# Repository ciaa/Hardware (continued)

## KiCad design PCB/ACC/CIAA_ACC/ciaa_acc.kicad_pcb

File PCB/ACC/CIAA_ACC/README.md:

# CIAA-ACC

Here you will find KiCad design files, [gerber files](output_files) and some [documentation](doc) for this board
developed by [INTI Argentina](http://www.inti.gob.ar/) - [CMNB](http://www.inti.gob.ar/microynanoelectronica/) with the collaboration of [ACSE](http://www.sase.com.ar/asociacion-civil-sistemas-embebidos), [CADIEEL](http://www.cadieel.org.ar) and [Emtech S.A.](http://www.emtech.com.ar) as part of the [CIAA project](http://www.proyecto-ciaa.com.ar/).
Also you can visit [CIAA-ACC Wiki Page](http://www.proyecto-ciaa.com.ar/devwiki/doku.php?id=desarrollo:ciaa_acc:ciaa_acc_inicio).

 - [Authors](doc/AUTHORS.md).
 - License: [CIAA Hardware license](../../../LICENSE).

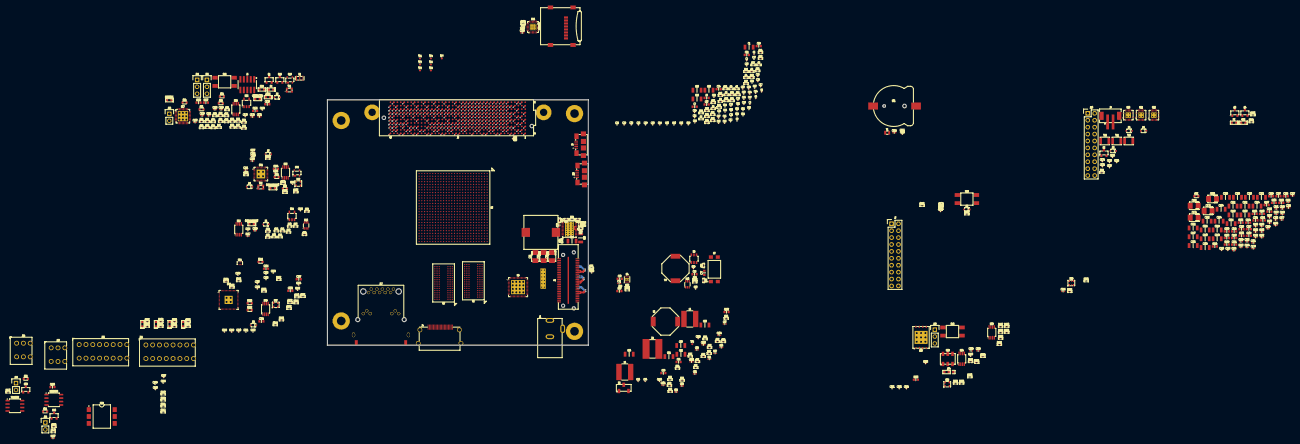
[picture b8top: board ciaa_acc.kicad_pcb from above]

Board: 12 copper layers, 571 parts (0 on the bottom side), 650 nets.

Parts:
BT1: CR1220; BC501SM
C1, C28, C55, C56, C65, C66, C80, C81, C82, C83, C86, C161, C163, C167, C180, C199, C203, C208, C216, C218, C220, C221, C222, C224, C226, C228, C230, C231, C232, C234: 100uF; c_1206
C2, C5, C10, C13, C16, C19, C22, C25, C29, C32, C37, C40, C43, C46, C49, C52, C59, C60, C69, C89, C93, C94, C95, C105, C106, C107, C108, C109, C110, C111, C115, C116, C123, C124, C132, C133, C134, C135, C136, C137, C142, C143, C144, C145, C146, C147, C148, C149, C151, C152, C153, C154, C248, C249, C250, C251, C253, C254, C255, C257, C258, C262, C263, C265, C267, C268: 100nF; c_0201
C3, C6, C8, C9, C11, C12, C14, C15, C17, C18, C20, C21, C23, C24, C26, C27, C30, C33, C35, C36, C38, C39, C41, C42, C44, C45, C47, C48, C50, C51, C53, C54, C61, C62, C63, C64, C150, C223, C225, C242, C243, C259, C269, C270, C271, C272, C273, C274, C275: 10nF; c_0201
C4, C7, C31, C34, C57, C58, C68, C70, C77, C90, C96, C122, C125, C126, C127, C155, C156, C160, C165, C169, C171, C173, C175, C178, C182, C184, C186, C188, C190, C194, C197, C204, C205, C206, C207, C209, C210, C211, C227, C229, C233, C246, C247, C252, C264: 10uF; c_0603
C67: 470nF; c_0402
C71: 220nF; c_0402
C72, C87: 2.2nF; c_0402
C73: 47nF; c_0402
C74: 22nF; c_0402
C75, C119, C120, C121: 1nF; c_0402
C76, C78, C79, C162, C166, C170, C174: 330uF; tant_B_3528
C84, C85, C97, C98: 68nF; c_0402
C88, C101: 1.2nF; c_0402
C91: 24pF; c_0402
C92: 11pF; c_0402
C99, C244: 4.7uF; c_0603
C100, C138, C139, C140, C141: 1.5nF; c_0402
C102: 3.3uF; c_0603
C103: 16pF; c_0402
C104: 13pF; c_0402
C112, C113: 18pF; c_0201
C114, C117, C118, C128, C129, C130, C131, C157, C158, C159, C238, C239, C240, C245, C256, C261, C266: 100nF; c_0402
C164, C168, C172, C176, C177, C179, C181, C183, C185, C187, C189, C191, C192, C193, C195, C196, C198, C200, C201, C202, C213, C215, C217, C219, C235, C236, C241, C260: 1uF; c_0402
C212, C214: 10uF; c_1206
C237: 2.2uF; c_0402
D1, D4, D5: PESD3V3U1UA; SOD-323
D2, D3, D6, D7, D9: 1N4148; SOD-323
D8: SD05T1G; SOD-323
DS1, DS11: OVERCURRENT; LED-0603
DS2, DS13: ERR; LED-0603
DS3, DS12: OK; LED-0603
DS4: DONE; LED-0603
DS5: CONNECTED; LED-0603
DS6: RUNNING; LED-0603
DS7, DS8, DS9, DS10: LED; LED-0603
FB1, FB2, FB10, FB11, FB12: MPZ1608S601ATA00; l_0603
FB3, FB7, FB8: BLM18KG221SN1D; l_0603
FB4, FB5, FB6, FB9: MMZ1608B601CTAH0; l_0603
H1, H2, H3, H4: PCB_HOLE; PCIE104_HOLE
J1: 5V 5A; POWER_JACK
J2: OneBank Top; ASP-129637-13
J3: OneBank Bottom; ASP-129646-22
J4: HDMI; 10029449-111RLF
J5: FMC_HPC; ASP-134486-01
J6: JTAG DIRECT; PIN_ARRAY_5x2_1.27_SMD
J7, J10: DNP; Pin_Header_Straight_2x10
J8: USB Micro B; ZX62-AB-5PA
J9: FAN; B2B-PH-SM4-TB
J11: DIGITAL IN; 1770940
J12: DIGITAL OUT; 1770940
J13: UART0; Pin_Header_Straight_1x03
J14: CAN; 1770898
J15: RS485; 1770898
J16: USB Micro AB; ZX62-AB-5PA
J17: 1840461-1
J18: microSD; MicroSD_Hinged
JP1, JP2: JUMPER3; Pin_Header_Straight_1x03
JP3, JP5, JP6: JUMPER; Pin_Header_Straight_1x02
JP4: PLL; JUMPER3_0603
L1: 220nH; SRP1238A
L2, L5: 3uH; SRU1048
L3, L6: 4.7uH; SRN6045
L4: 6.2uH; SRR6038
Q1: DMP3099L; SOT-23
Q2, Q3, Q4: BSS806N; SOT-23
R1, R2, R27: 80.6; r_0402
R3, R4, R5, R6, R7, R8, R9, R10, R11, R12, R13, R14, R15, R16, R17, R18, R19, R20, R21, R22, R23, R24, R25, R26: 40.2; r_0402
R28, R79, R80, R92, R125, R130, R131, R133, R140, R145: 4.7K; r_0402
R29, R30: 240; r_0402
R31, R32, R45, R46, R50, R57, R59, R64, R119, R120, R141, R142, R146: 10K; r_0402
R33: 200K; r_0402
R34, R36, R49, R98: 100K; r_0402
R35, R103, R104, R105, R106, R135, R147, R148, R152: 1K; r_0402
R37: 309K; r_0402
R38: 2; r_0402
R39: 10.7K; r_0402
R40: 174K; r_0402
R41: 39.2K; r_0402
R42: 3; r_0402
R43, R81, R82, R83, R84, R85, R86, R115, R116, R137, R143, R153: 100; r_0402
R44: 6.49K; r_0402
R47: 6.81K; r_0402
R48: 8.87K; r_0402
R51, R121, R122, R123, R124, R126, R129: 20K; r_0402
R52, R63: 16K; r_0402
R53: 6.65K; r_0402
R54: 13.3K; r_0402
R55: 11.3K; r_0402
R56: 11K; r_0402
R58: 182K; r_0402
R60: 75K; r_0402
R61: 24K; r_0402
R62: 14K; r_0402
R65: 5.1K; r_0402
R66, R67, R149: DNP; r_0402
R68, R69, R70, R71, R72, R73, R74, R76, R132: 49R9; r_0402
R75: 51K; r_0402
R77: 27K; r_0402
R78, R134: 680; r_0402
R87: 2K2; r_0402
R88: 3K3; r_0402
R89: 1.5K; r_0402
R90, R91, R95, R97: 33; r_0402
R93, R155: 330; r_0402
R94, R96, R150, R151, R154: 220; r_0402
R99, R100, R101, R102: 4.7K 1/4W; r_1206
R107, R108, R109, R110: 33K; r_0402
R111, R112, R113, R114: 560; r_0402
R117, R118: 2.2K; r_0402
R127, R128: 120; r_0402
R136: 8.06K; r_0402
R138, R139: 1.0K; r_0402
R144: 12.1K; r_0402
RP1: 10K; r_0402_4
SW1: PROG_B; TACT_SMD_4.5X4.5
SW2: POR_B; TACT_SMD_4.5X4.5
SW3: SRST; TACT_SMD_4.5X4.5
TH1, TH2, TH3: PTC 0.5A; ptc_1210
TP1, TP2, TP3, TP4, TP5, TP6, TP7, TP8: TESTPOINT
TR1, TR2: SRF2012
U1: XC7Z030-2FBG676I; FBG676
U2, U3: MT41K256M16TW-107 IT; FBGA96
U4: TPS51206
U5: TPS53355
U6: CJS-1200TA
U7: LTV-817S; OPTO_SMD
U8: TPS563209; SOT-23-6
U9: TPS65400
U10: MCP4017; SC-70-6
U11: CBTL04083A; HVQFN42
U12: MCP79410; MSOP-8
U13: TXB0101; SC-70-6
U14: MIC2090; SOT-23-5
U15: ADP122; SOT-23-5
U16: REF3012; SOT-23
U17: LPC11U35FHI33; LPC11U35
U18, U24, U25, U26, U27, U33, U34, U48: 74AVC2T45; MSOP-8
U19, U44: CM1213A; SOT-143
U20, U21, U22: LSF0204D
U23: TLP290-4; SOIC-16
U28, U29, U30, U31: VO14642AABTR; DIP-6-SMD
U32: 33.33MHz; ABRACON-ASDMB
U35: XR33038; SOIC-8
U36: TCAN332; SOIC-8
U37: QSPI; WSON-8
U38: CAS-D20TA
U39, U40: PESD1CAN; SOT-23
U41: USB3320C
U42: 24MHz; ABRACON-ASDMB
U43: MIC2025; MSOP-8
U45: KSZ9031RNXIA; KSZ9031RNX
U46: TXS02612
U47: 25MHz; ABRACON-ASDMB
U49: DSC1123DL5-200.0000; DSC1123D
X1: 12MHz; CSTCE_G
Y1: 32K; ABRACON-ABS06

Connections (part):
+1.0V: C74.2, C76.1, C78.1, C79.1, C161.2, C162.1, C163.2, C164.2, C165.2, C166.1, C167.2, C168.2, C169.2, C170.1, C171.2, C172.2, C173.2, C174.1, C175.2, C176.2, C177.2, C178.2, C179.2, C181.2, C182.2, C183.2, C185.2, C186.2, C187.2, C189.2, C190.2, C191.2, C193.2, C194.2, C195.2, C197.2, C198.2, C201.2, C202.2, C205.2, L1.2, R44.2, U1.AA4, U1.AA8, U1.AB6, U1.AC8, U1.AD6, U1.AE8, U1.L11, U1.L13, U1.L15, U1.L17, U1.M12, U1.M16, U1.N11, U1.N15, U1.N17, U1.P12, U1.P16, U1.P18, U1.R4, U1.R11, U1.R15, U1.R17, U1.T6, U1.T12, U1.T14, U1.T16, U1.T18, U1.U4, U1.U11, U1.U13, U1.U15, U1.U17, U1.V16, U1.Y6
+1.2V: C80.2, C204.2, C252.1, C253.1, C254.1, C255.1, FB11.1, FB12.1, L4.2, R53.1, R115.1, U1.AB2, U1.AB7, U1.AC4, U1.AD2, U1.AE4, U1.AF2, U1.AF6, U1.T2, U1.V2, U1.W4, U1.Y2, U45.14, U45.18, U45.23, U45.26, U45.30, U45.39
+1.5V: C1.2, C2.2, C3.1, C4.2, C5.2, C6.1, C7.2, C8.1, C9.1, C10.2, C11.1, C12.1, C13.2, C14.1, C15.1, C16.2, C17.1, C18.1, C19.2, C20.1, C21.1, C22.2, C23.1, C24.1, C25.2, C26.1, C27.1, C28.2, C29.2, C30.1, C31.2, C32.2, C33.1, C34.2, C35.1, C36.1, C37.2, C38.1, C39.1, C40.2, C41.1, C42.1, C43.2, C44.1, C45.1, C46.2, C47.1, C48.1, C49.2, C50.1, C51.1, C52.2, C53.1, C54.1, C81.2, C208.2, C210.2, C211.2, C213.2, C215.2, C217.2, C219.2, C220.2, C222.2, C224.2, C226.2, C228.2, C230.2, C232.2, C234.2, L6.2, R1.2, R62.1, U1.H25, U1.J22, U1.L26, U1.M23, U1.N20, U1.R24, U1.T21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
+1.8V: C82.2, C180.2, C184.2, C188.2, C192.2, C196.2, C199.2, C200.2, C203.2, C206.2, C231.2, C233.2, C235.2, C236.2, C238.1, C239.1, C240.1, C243.2, C247.1, C248.1, C249.1, C256.2, C262.1, FB7.2, L3.2, R51.1, R131.2, R139.2, R140.1, RP1.1, RP1.2, RP1.3, RP1.4, U1.C20, U1.D17, U1.F21, U1.G18, U1.K18, U1.L19, U1.M10, U1.N9, U1.N19, U1.P8, U1.P10, U1.R9, U1.R19, U1.T8, U1.T10, U1.U9, U1.U19, U1.V6, U1.V10, U6.1, U9.27, U9.34, U22.1, U41.8, U41.11, U41.14, U41.28, U41.30, U41.32, U42.1, U42.4, U45.16, U45.34, U45.40, U46.5, U48.8
+3.3V: C68.1, C69.1, C83.2, C109.2, C110.2, C111.2, C114.2, C127.2, C128.2, C129.1, C130.2, C133.1, C135.1, C137.1, C143.1, C145.1, C147.1, C149.1, C150.2, C152.1, C154.1, C155.2, C156.2, C157.2, C158.2, C159.2, C207.2, C209.2, C227.2, C229.2, C237.1, C246.1, C259.1, C260.2, C261.2, C263.1, C266.2, DS2.1, DS4.1, DS7.1, DS8.1, DS9.1, DS10.1, DS12.1, DS13.1, FB10.1, J5.C39, J5.D32, J5.D36, J5.D38, J5.D40, J6.1, J17.12, J18.4, JP4.1, L5.2, Q1.2, R31.2, R32.2, R60.1, R80.2, R92.2, R107.2, R108.2, R109.2, R110.2, R117.2, R118.2, R119.1, R120.1, R121.1, R130.1, R149.1, TH3.1, U1.A26, U1.B23, U1.E24, U1.T7, U1.U8, U1.V8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
+5V: C65.2, C66.2, C77.1, C86.1, C93.1, C116.1, C117.2, C241.1, DS11.1, FB1.1, J1.1, J2.53, J3.53, R33.1, R66.2, R67.2, R78.1, TH1.2, TH2.1, U5.12, U5.13, U5.14, U5.15, U5.16, U5.17, U5.19, U7.4, U8.3, U9.5, U9.6, U9.22, U9.30, U9.31, U10.1, U13.6, U14.1, U43.7
/Principal/BANKS_HP/FAN_PWM: Q2.1, R98.1, U1.H16
/Principal/BANKS_HP/FMC_CLK1_C2M_N: J5.J3, U1.H14
/Principal/BANKS_HP/FMC_CLK1_C2M_P: J5.J2, U1.J14
/Principal/BANKS_HP/FMC_CLK1_M2C_N: J5.K5, U1.D14
/Principal/BANKS_HP/FMC_CLK1_M2C_P: J5.K4, U1.D15
/Principal/BANKS_HP/FMC_HA_0_N: J5.F5, U1.J3
/Principal/BANKS_HP/FMC_HA_0_P: J5.F4, U1.J4
/Principal/BANKS_HP/FMC_HA_1_N: J5.E3, U1.M5
/Principal/BANKS_HP/FMC_HA_1_P: J5.E2, U1.M6
/Principal/BANKS_HP/FMC_HA_2_N: J5.K8, U1.F4
/Principal/BANKS_HP/FMC_HA_2_P: J5.K7, U1.G4
/Principal/BANKS_HP/FMC_HA_3_N: J5.J7, U1.D3
/Principal/BANKS_HP/FMC_HA_3_P: J5.J6, U1.D4
/Principal/BANKS_HP/FMC_HA_4_N: J5.F8, U1.F2
/Principal/BANKS_HP/FMC_HA_4_P: J5.F7, U1.G2
/Principal/BANKS_HP/FMC_HA_5_N: J5.E7, U1.C1
/Principal/BANKS_HP/FMC_HA_5_P: J5.E6, U1.D1
/Principal/BANKS_HP/FMC_HA_6_N: J5.K11, U1.E1
/Principal/BANKS_HP/FMC_HA_6_P: J5.K10, U1.E2
/Principal/BANKS_HP/FMC_HA_7_N: J5.J10, U1.E3
/Principal/BANKS_HP/FMC_HA_7_P: J5.J9, U1.F3
/Principal/BANKS_HP/FMC_HA_8_N: J5.F11, U1.H1
/Principal/BANKS_HP/FMC_HA_8_P: J5.F10, U1.J1
/Principal/BANKS_HP/FMC_HA_9_N: J5.E10, U1.H3
/Principal/BANKS_HP/FMC_HA_9_P: J5.E9, U1.H4
/Principal/BANKS_HP/FMC_HA_10_N: J5.K14, U1.K1
/Principal/BANKS_HP/FMC_HA_10_P: J5.K13, U1.K2
/Principal/BANKS_HP/FMC_HA_11_N: J5.J13, U1.G1
/Principal/BANKS_HP/FMC_HA_11_P: J5.J12, U1.H2
/Principal/BANKS_HP/FMC_HA_12_N: J5.F14, U1.K3
/Principal/BANKS_HP/FMC_HA_12_P: J5.F13, U1.L3
/Principal/BANKS_HP/FMC_HA_13_N: J5.E13, U1.N2
/Principal/BANKS_HP/FMC_HA_13_P: J5.E12, U1.N3
/Principal/BANKS_HP/FMC_HA_14_N: J5.J16, U1.L2
/Principal/BANKS_HP/FMC_HA_14_P: J5.J15, U1.M2
/Principal/BANKS_HP/FMC_HA_15_N: J5.F17, U1.M4
/Principal/BANKS_HP/FMC_HA_15_P: J5.F16, U1.N4
/Principal/BANKS_HP/FMC_HA_16_N: J5.E16, U1.M1
/Principal/BANKS_HP/FMC_HA_16_P: J5.E15, U1.N1
/Principal/BANKS_HP/FMC_HA_17_N: J5.K17, U1.L4
/Principal/BANKS_HP/FMC_HA_17_P: J5.K16, U1.L5
/Principal/BANKS_HP/FMC_HA_18_N: J5.J19, U1.L7
/Principal/BANKS_HP/FMC_HA_18_P: J5.J18, U1.M7
/Principal/BANKS_HP/FMC_HA_19_N: J5.F20, U1.J5
/Principal/BANKS_HP/FMC_HA_19_P: J5.F19, U1.K5
/Principal/BANKS_HP/FMC_HA_20_N: J5.E19, U1.L8
/Principal/BANKS_HP/FMC_HA_20_P: J5.E18, U1.M8
/Principal/BANKS_HP/FMC_HA_21_N: J5.K20, U1.J6
/Principal/BANKS_HP/FMC_HA_21_P: J5.K19, U1.K6
/Principal/BANKS_HP/FMC_HA_22_N: J5.J22, U1.N6
/Principal/BANKS_HP/FMC_HA_22_P: J5.J21, U1.N7
/Principal/BANKS_HP/FMC_HA_23_N: J5.K23, U1.K7
/Principal/BANKS_HP/FMC_HA_23_P: J5.K22, U1.K8
/Principal/BANKS_HP/FMC_HB_0_N: J5.K26, U1.E7
/Principal/BANKS_HP/FMC_HB_0_P: J5.K25, U1.F8
/Principal/BANKS_HP/FMC_HB_1_N: J5.J25, U1.H11
/Principal/BANKS_HP/FMC_HB_1_P: J5.J24, U1.J11
/Principal/BANKS_HP/FMC_HB_2_N: J5.F23, U1.G5
/Principal/BANKS_HP/FMC_HB_2_P: J5.F22, U1.G6
/Principal/BANKS_HP/FMC_HB_3_N: J5.E22, U1.H6
/Principal/BANKS_HP/FMC_HB_3_P: J5.E21, U1.H7
/Principal/BANKS_HP/FMC_HB_4_N: J5.F26, U1.J9
/Principal/BANKS_HP/FMC_HB_4_P: J5.F25, U1.J10
/Principal/BANKS_HP/FMC_HB_5_N: J5.E25, U1.H8
/Principal/BANKS_HP/FMC_HB_5_P: J5.E24, U1.J8
/Principal/BANKS_HP/FMC_HB_6_N: J5.K29, U1.C7
/Principal/BANKS_HP/FMC_HB_6_P: J5.K28, U1.C8
/Principal/BANKS_HP/FMC_HB_7_N: J5.J28, U1.E5
/Principal/BANKS_HP/FMC_HB_7_P: J5.J27, U1.F5
/Principal/BANKS_HP/FMC_HB_8_N: J5.F29, U1.D8
/Principal/BANKS_HP/FMC_HB_8_P: J5.F28, U1.D9
/Principal/BANKS_HP/FMC_HB_9_N: J5.E28, U1.E8
/Principal/BANKS_HP/FMC_HB_9_P: J5.E27, U1.F9
/Principal/BANKS_HP/FMC_HB_10_N: J5.K32, U1.D5
/Principal/BANKS_HP/FMC_HB_10_P: J5.K31, U1.E6
/Principal/BANKS_HP/FMC_HB_11_N: J5.J31, U1.B9
/Principal/BANKS_HP/FMC_HB_11_P: J5.J30, U1.C9
/Principal/BANKS_HP/FMC_HB_12_N: J5.F32, U1.A10
/Principal/BANKS_HP/FMC_HB_12_P: J5.F31, U1.B10
/Principal/BANKS_HP/FMC_HB_13_N: J5.E31, U1.A8
/Principal/BANKS_HP/FMC_HB_13_P: J5.E30, U1.A9
/Principal/BANKS_HP/FMC_HB_14_N: J5.K35, U1.A7
/Principal/BANKS_HP/FMC_HB_14_P: J5.K34, U1.B7
/Principal/BANKS_HP/FMC_HB_15_N: J5.J34, U1.C3
/Principal/BANKS_HP/FMC_HB_15_P: J5.J33, U1.C4
/Principal/BANKS_HP/FMC_HB_16_N: J5.F35, U1.B4
/Principal/BANKS_HP/FMC_HB_16_P: J5.F34, U1.B5
/Principal/BANKS_HP/FMC_HB_17_N: J5.K38, U1.C6
/Principal/BANKS_HP/FMC_HB_17_P: J5.K37, U1.D6
/Principal/BANKS_HP/FMC_HB_18_N: J5.J37, U1.A5
/Principal/BANKS_HP/FMC_HB_18_P: J5.J36, U1.B6
/Principal/BANKS_HP/FMC_HB_19_N: J5.E34, U1.A3
/Principal/BANKS_HP/FMC_HB_19_P: J5.E33, U1.A4
/Principal/BANKS_HP/FMC_HB_20_N: J5.F38, U1.B1
/Principal/BANKS_HP/FMC_HB_20_P: J5.F37, U1.C2
/Principal/BANKS_HP/FMC_HB_21_N: J5.E37, U1.A2
/Principal/BANKS_HP/FMC_HB_21_P: J5.E36, U1.B2
/Principal/BANKS_HP/GPIO0: U1.J13, U20.2
/Principal/BANKS_HP/GPIO1: U1.K13, U20.3
/Principal/BANKS_HP/GPIO2: U1.J15, U20.4
/Principal/BANKS_HP/GPIO3: U1.K15, U20.5
/Principal/BANKS_HP/GPIO4: U1.G15, U21.2
/Principal/BANKS_HP/GPIO5: U1.G16, U21.3
/Principal/BANKS_HP/GPIO6: U1.F14, U21.4
/Principal/BANKS_HP/GPIO7: U1.G14, U21.5
/Principal/BANKS_HP/SYSCLK_N: R153.1, U1.F7, U49.5
/Principal/BANKS_HP/SYSCLK_P: R153.2, U1.G7, U49.4
/Principal/BANKS_HP/VADJ_EN: R43.1, U1.K12
/Principal/BANKS_HP/XADC_AD0_B_N: C120.2, R83.1, U1.E12
/Principal/BANKS_HP/XADC_AD0_B_P: C120.1, R84.1, U1.F12
/Principal/BANKS_HP/XADC_AD8_B_N: C121.2, R85.1, U1.D10
/Principal/BANKS_HP/XADC_AD8_B_P: C121.1, R86.1, U1.E10
/Principal/BANKS_HP/XADC_GPIO_0: J7.18, U1.F10
/Principal/BANKS_HP/XADC_GPIO_1: J7.17, U1.G10
/Principal/BANKS_HP/XADC_GPIO_2: J7.20, U1.D11
/Principal/BANKS_HP/XADC_GPIO_3: J7.19, U1.E11
/Principal/BANKS_HR/CAN_RX: U1.AF19, U36.4
/Principal/BANKS_HR/CAN_TX: U1.AF20, U36.1
/Principal/BANKS_HR/DIN0: U1.AE21, U24.2
/Principal/BANKS_HR/DIN1: U1.AE20, U24.3
/Principal/BANKS_HR/DIN2: U1.AD19, U25.2
/Principal/BANKS_HR/DIN3: U1.AD18, U25.3
/Principal/BANKS_HR/DOUT0: U1.AF18, U26.7
/Principal/BANKS_HR/DOUT1: U1.AE18, U26.6
/Principal/BANKS_HR/DOUT2: U1.Y20, U27.7
/Principal/BANKS_HR/DOUT3: U1.W20, U27.6
/Principal/BANKS_HR/FMC_CLK0_C2M_N: J5.G3, U1.AC24
/Principal/BANKS_HR/FMC_CLK0_C2M_P: J5.G2, U1.AC23
/Principal/BANKS_HR/FMC_CLK0_M2C_N: J5.H5, U1.AD21
/Principal/BANKS_HR/FMC_CLK0_M2C_P: J5.H4, U1.AD20
/Principal/BANKS_HR/FMC_LA_0_N: J5.G7, U1.AD11
/Principal/BANKS_HR/FMC_LA_0_P: J5.G6, U1.AC12
/Principal/BANKS_HR/FMC_LA_1_N: J5.D9, U1.AD13
/Principal/BANKS_HR/FMC_LA_1_P: J5.D8, U1.AC13
/Principal/BANKS_HR/FMC_LA_2_N: J5.H8, U1.Y11
/Principal/BANKS_HR/FMC_LA_2_P: J5.H7, U1.Y12
/Principal/BANKS_HR/FMC_LA_3_N: J5.G10, U1.AC11
/Principal/BANKS_HR/FMC_LA_3_P: J5.G9, U1.AB12
/Principal/BANKS_HR/FMC_LA_4_N: J5.H11, U1.AA10
/Principal/BANKS_HR/FMC_LA_4_P: J5.H10, U1.Y10
/Principal/BANKS_HR/FMC_LA_5_N: J5.D12, U1.AB10
/Principal/BANKS_HR/FMC_LA_5_P: J5.D11, U1.AB11
/Principal/BANKS_HR/FMC_LA_6_N: J5.C11, U1.Y13
/Principal/BANKS_HR/FMC_LA_6_P: J5.C10, U1.W13
/Principal/BANKS_HR/FMC_LA_7_N: J5.H14, U1.AA12
/Principal/BANKS_HR/FMC_LA_7_P: J5.H13, U1.AA13
/Principal/BANKS_HR/FMC_LA_8_N: J5.G13, U1.AD10
/Principal/BANKS_HR/FMC_LA_8_P: J5.G12, U1.AE10
/Principal/BANKS_HR/FMC_LA_9_N: J5.D15, U1.AF12
/Principal/BANKS_HR/FMC_LA_9_P: J5.D14, U1.AE12
/Principal/BANKS_HR/FMC_LA_10_N: J5.C15, U1.AF10
/Principal/BANKS_HR/FMC_LA_10_P: J5.C14, U1.AE11
/Principal/BANKS_HR/FMC_LA_11_N: J5.H17, U1.AF13
/Principal/BANKS_HR/FMC_LA_11_P: J5.H16, U1.AE13
/Principal/BANKS_HR/FMC_LA_12_N: J5.G16, U1.AD15
/Principal/BANKS_HR/FMC_LA_12_P: J5.G15, U1.AD16
/Principal/BANKS_HR/FMC_LA_13_N: J5.D18, U1.AF14
/Principal/BANKS_HR/FMC_LA_13_P: J5.D17, U1.AF15
/Principal/BANKS_HR/FMC_LA_14_N: J5.C19, U1.AE15
/Principal/BANKS_HR/FMC_LA_14_P: J5.C18, U1.AE16
/Principal/BANKS_HR/FMC_LA_15_N: J5.H20, U1.AF17
/Principal/BANKS_HR/FMC_LA_15_P: J5.H19, U1.AE17
/Principal/BANKS_HR/FMC_LA_16_N: J5.G19, U1.AA17
/Principal/BANKS_HR/FMC_LA_16_P: J5.G18, U1.Y17
/Principal/BANKS_HR/FMC_LA_17_N: J5.D21, U1.AD14
/Principal/BANKS_HR/FMC_LA_17_P: J5.D20, U1.AC14
/Principal/BANKS_HR/FMC_LA_18_N: J5.C23, U1.AB14
/Principal/BANKS_HR/FMC_LA_18_P: J5.C22, U1.AB15
/Principal/BANKS_HR/FMC_LA_19_N: J5.H23, U1.AB16
/Principal/BANKS_HR/FMC_LA_19_P: J5.H22, U1.AB17
/Principal/BANKS_HR/FMC_LA_20_N: J5.G22, U1.AC16
/Principal/BANKS_HR/FMC_LA_20_P: J5.G21, U1.AC17
/Principal/BANKS_HR/FMC_LA_21_N: J5.H26, U1.AA14
/Principal/BANKS_HR/FMC_LA_21_P: J5.H25, U1.AA15
/Principal/BANKS_HR/FMC_LA_22_N: J5.G25, U1.Y15
/Principal/BANKS_HR/FMC_LA_22_P: J5.G24, U1.Y16
/Principal/BANKS_HR/FMC_LA_23_N: J5.D24, U1.W15
/Principal/BANKS_HR/FMC_LA_23_P: J5.D23, U1.W16
/Principal/BANKS_HR/FMC_LA_24_N: J5.H29, U1.AB25
/Principal/BANKS_HR/FMC_LA_24_P: J5.H28, U1.AA25
/Principal/BANKS_HR/FMC_LA_25_N: J5.G28, U1.AC26
/Principal/BANKS_HR/FMC_LA_25_P: J5.G27, U1.AB26
/Principal/BANKS_HR/FMC_LA_26_N: J5.D27, U1.AE26
/Principal/BANKS_HR/FMC_LA_26_P: J5.D26, U1.AE25
/Principal/BANKS_HR/FMC_LA_27_N: J5.C27, U1.AD26
/Principal/BANKS_HR/FMC_LA_27_P: J5.C26, U1.AD25
/Principal/BANKS_HR/FMC_LA_28_N: J5.H32, U1.AF25
/Principal/BANKS_HR/FMC_LA_28_P: J5.H31, U1.AF24
/Principal/BANKS_HR/FMC_LA_29_N: J5.G31, U1.AB24
/Principal/BANKS_HR/FMC_LA_29_P: J5.G30, U1.AA24
/Principal/BANKS_HR/FMC_LA_30_N: J5.H35, U1.AF22
/Principal/BANKS_HR/FMC_LA_30_P: J5.H34, U1.AE22
/Principal/BANKS_HR/FMC_LA_31_N: J5.G34, U1.AF23
/Principal/BANKS_HR/FMC_LA_31_P: J5.G33, U1.AE23
/Principal/BANKS_HR/FMC_LA_32_N: J5.H38, U1.AB22
/Principal/BANKS_HR/FMC_LA_32_P: J5.H37, U1.AB21
/Principal/BANKS_HR/FMC_LA_33_N: J5.G37, U1.AA23
/Principal/BANKS_HR/FMC_LA_33_P: J5.G36, U1.AA22
/Principal/BANKS_HR/FMC_PRSNT: D2.1, R79.2, U1.Y18
/Principal/BANKS_HR/HDMI_CEC: D1.2, J4.13, R77.1, U1.V19
/Principal/BANKS_HR/HDMI_HPD: U1.V18, U13.3
/Principal/BANKS_HR/HDMI_OUT_EN: U1.AC22, U14.3
/Principal/BANKS_HR/LED_ERR: Q4.1, U1.W17
/Principal/BANKS_HR/LED_OK: Q3.1, U1.W14
/Principal/BANKS_HR/MGTREFCLK1_B_N: C267.1, J5.D5
/Principal/BANKS_HR/MGTREFCLK1_B_P: C268.1, J5.D4
/Principal/BANKS_HR/MGTREFCLK1_N: C267.2, U1.U5
/Principal/BANKS_HR/MGTREFCLK1_P: C268.2, U1.U6
/Principal/BANKS_HR/RS485_ENA: U1.AA18, U33.6
/Principal/BANKS_HR/TMDS_CLK_N: J4.12, R76.2, U1.W19
/Principal/BANKS_HR/TMDS_CLK_P: J4.10, R74.2, U1.W18
/Principal/BANKS_HR/TMDS_D0_N: J4.9, R73.2, U1.AB20
/Principal/BANKS_HR/TMDS_D0_P: J4.7, R72.2, U1.AA20
/Principal/BANKS_HR/TMDS_D1_N: J4.6, R71.2, U1.AC19
/Principal/BANKS_HR/TMDS_D1_P: J4.4, R70.2, U1.AC18
/Principal/BANKS_HR/TMDS_D2_N: J4.3, R69.2, U1.AB19
/Principal/BANKS_HR/TMDS_D2_P: J4.1, R68.2, U1.AA19
/Principal/BANKS_HR/UART_EMIO_RX: TP7.1, U1.AD24, U34.2
/Principal/BANKS_HR/UART_EMIO_TX: TP8.1, U1.AD23, U33.7
/Principal/BANK_0/CHS_DBG: FB4.2, J8.6, U19.1
/Principal/BANK_0/DBG_USB_B_N: J8.2, TR1.4, U19.3
/Principal/BANK_0/DBG_USB_B_P: J8.3, TR1.1, U19.2
/Principal/BANK_0/DBG_USB_N: R90.1, TR1.3
/Principal/BANK_0/DBG_USB_P: R89.2, R91.1, TR1.2
/Principal/BANK_0/DBG_VBUS: FB3.1, R87.2
/Principal/BANK_0/DBG_VBUS_B: C131.2, FB3.2, J8.1, U19.4
/Principal/BANK_0/DBG_VBUS_DIV: R87.1, R88.2, U17.9
/Principal/BANK_0/FPGA_DONE: U1.W9, U18.6
/Principal/BANK_0/I2C_SCL: D5.2, J4.15, J10.20, R117.1, TP4.1, U1.A23, U9.43, U10.3, U12.6, U17.10
/Principal/BANK_0/I2C_SDA: D4.2, J4.16, J10.19, R118.1, TP5.1, U1.B25, U9.42, U10.4, U12.5, U17.11
/Principal/BANK_0/INIT_B: R92.1, U1.R8, U18.7
/Principal/BANK_0/LED_CON: R96.2, U17.21
/Principal/BANK_0/LED_RUN: R97.2, U17.22
/Principal/BANK_0/LPC_UART_RX: TP6.1, U1.B26, U17.31
/Principal/BANK_0/LPC_UART_TX: TP1.1, U1.A25, U17.32
/Principal/BANK_0/POWERGOOD: J5.D1, R57.1, SW2.3, TP3.1, U1.C23, U9.17
/Principal/BANK_0/SMBUS_SCL: J2.49, J3.49, J5.C30, R119.2, U1.D23
/Principal/BANK_0/SMBUS_SDA: J2.47, J3.47, J5.C31, R120.2, U1.C24
/Principal/BANK_0/TCK: J5.D29, J6.4, U1.W12, U17.16
/Principal/BANK_0/TDI: J6.8, U1.V11, U17.30
/Principal/BANK_0/TDO: J5.D31, J6.6, JP1.1, U17.18
/Principal/BANK_0/TMS: J5.D33, J6.2, U1.W11, U17.17
/Principal/BANK_0/XADC_5V: C122.2, FB1.2, J7.13, U15.1, U15.3, U16.1
/Principal/BANK_0/XADC_AD0_N: J7.6, R83.2
/Principal/BANK_0/XADC_AD0_P: J7.3, R84.2
/Principal/BANK_0/XADC_AD8_N: J7.7, R85.2
/Principal/BANK_0/XADC_AD8_P: J7.8, R86.2
/Principal/BANK_0/XADC_DXN: J7.12, U1.R13
/Principal/BANK_0/XADC_DXP: J7.9, U1.R14
/Principal/BANK_0/XADC_VN_B_N: C119.2, R81.1, U1.P13
/Principal/BANK_0/XADC_VN_N: J7.1, R81.2
/Principal/BANK_0/XADC_VP_B_P: C119.1, R82.1, U1.N14
/Principal/BANK_0/XADC_VP_P: J7.2, R82.2
/Principal/BANK_0/XADC_VREF: C126.2, J7.11, JP2.1, U16.2
/Principal/BANK_0/XADC_VREFP: C124.1, JP2.2, U1.P14
/Principal/BANK_112/DP0_C2M_N: J5.C3, U1.W1
/Principal/BANK_112/DP0_C2M_P: J5.C2, U1.W2
/Principal/BANK_112/DP0_M2C_N: J5.C7, U1.Y3
/Principal/BANK_112/DP0_M2C_P: J5.C6, U1.Y4
/Principal/BANK_112/DP1_C2M_N: J5.A23, U1.U1
/Principal/BANK_112/DP1_C2M_P: J5.A22, U1.U2
/Principal/BANK_112/DP1_M2C_N: J5.A3, U1.V3
/Principal/BANK_112/DP1_M2C_P: J5.A2, U1.V4
/Principal/BANK_112/DP2_C2M_N: J5.A27, U1.R1
/Principal/BANK_112/DP2_C2M_P: J5.A26, U1.R2
/Principal/BANK_112/DP2_M2C_N: J5.A7, U1.T3
/Principal/BANK_112/DP2_M2C_P: J5.A6, U1.T4
/Principal/BANK_112/MGTREFCLK0_N: U1.R5, U11.12
/Principal/BANK_112/MGTREFCLK0_P: U1.R6, U11.11
/Principal/BANK_112/MGTXRX0_N: U1.AB3, U11.3
/Principal/BANK_112/MGTXRX0_P: U1.AB4, U11.2
/Principal/BANK_112/MGTXTX0_N: C108.1, U1.AA1
/Principal/BANK_112/MGTXTX0_P: C107.1, U1.AA2
/Principal/BANK_500/CAN_N: J14.2, R127.2, U36.6, U39.2
/Principal/BANK_500/CAN_P: J14.1, JP5.2, U36.7, U39.1
/Principal/BANK_500/ETH_RST: D9.2, R124.1, U1.E23
/Principal/BANK_500/QSPI_CS: R130.2, U1.D26, U37.1
/Principal/BANK_500/QSPI_IO0: R122.1, U1.E25, U37.5
/Principal/BANK_500/QSPI_IO1: R123.1, U1.D25, U37.2
/Principal/BANK_500/QSPI_IO2: R126.2, U1.F24, U37.3
/Principal/BANK_500/QSPI_IO3: R129.1, U1.C26, U37.7
/Principal/BANK_500/QSPI_SCK: JP4.2, U1.F23, U37.6
/Principal/BANK_500/RS485_ENA_B: R125.1, U33.3, U35.2, U35.3
/Principal/BANK_500/RS485_N: J15.2, R128.2, U35.7, U40.2
/Principal/BANK_500/RS485_P: J15.1, JP6.2, U35.6, U40.1
/Principal/BANK_500/UART_485_RX: U1.D24, U35.1
/Principal/BANK_500/UART_485_TX: R121.2, U1.A24, U35.4
/Principal/BANK_500/UART_EMIO_RX_B: J13.2, U34.7
/Principal/BANK_500/UART_EMIO_TX_B: J13.1, U33.2
/Principal/BANK_500/USB_RST: D7.2, U1.E26
/Principal/BANK_501/AVDDH: C250.1, C251.1, FB10.2, U45.1, U45.12
/Principal/BANK_501/AVDDL: C257.1, C258.1, FB11.2, U45.4, U45.9
/Principal/BANK_501/AVDDL_PLL: C264.1, C265.1, FB12.2, U45.44
/Principal/BANK_501/CHS_OTG: FB9.2, J16.6, U44.1
/Principal/BANK_501/ETH_LED1: R148.1, U45.17, U48.7
/Principal/BANK_501/ETH_LED2: R147.1, U45.15, U48.6
/Principal/BANK_501/ETH_LEDM: R146.1, U45.41
/Principal/BANK_501/ETH_MDC: U1.A20, U45.36
/Principal/BANK_501/ETH_MDIO: R140.2, U1.A19, U45.37
/Principal/BANK_501/ETH_RX0: RP1.8, U1.F20, U45.32
/Principal/BANK_501/ETH_RX1: RP1.7, U1.J19, U45.31
/Principal/BANK_501/ETH_RX2: RP1.6, U1.F19, U45.28
/Principal/BANK_501/ETH_RX3: RP1.5, U1.H17, U45.27
/Principal/BANK_501/ETH_RX_CLK: R141.2, U1.G22, U45.35
/Principal/BANK_501/ETH_RX_CTL: R142.2, U1.F18, U45.33
/Principal/BANK_501/ETH_TX0: U1.G17, U45.19
/Principal/BANK_501/ETH_TX1: U1.G20, U45.20
/Principal/BANK_501/ETH_TX2: U1.G19, U45.21
/Principal/BANK_501/ETH_TX3: U1.H19, U45.22
/Principal/BANK_501/ETH_TX_CLK: U1.G21, U45.24
/Principal/BANK_501/ETH_TX_CTL: U1.F22, U45.25
/Principal/BANK_501/MDI1_N: J17.2, U45.3
/Principal/BANK_501/MDI1_P: J17.1, U45.2
/Principal/BANK_501/MDI2_N: J17.4, U45.6
/Principal/BANK_501/MDI2_P: J17.3, U45.5
/Principal/BANK_501/MDI3_N: J17.6, U45.8
/Principal/BANK_501/MDI3_P: J17.5, U45.7
/Principal/BANK_501/MDI4_N: J17.8, U45.11
/Principal/BANK_501/MDI4_P: J17.7, U45.10
/Principal/BANK_501/OTG_VBUS_B: C244.1, C245.1, FB8.2, J16.1, R135.2, U44.4
/Principal/BANK_501/PS_SRST_B: D6.2, J5.D34, J6.10, U17.8
/Principal/BANK_501/SDIO_CLK: R132.1, U46.9
/Principal/BANK_501/SDIO_CMD: U1.C19, U46.4
/Principal/BANK_501/SDIO_D0: U1.F17, U46.6
/Principal/BANK_501/SDIO_D1: U1.D18, U46.7
/Principal/BANK_501/SDIO_D2: U1.E18, U46.1
/Principal/BANK_501/SDIO_D3: U1.C18, U46.3
/Principal/BANK_501/SPI_CLK: U1.B21, U22.4
/Principal/BANK_501/SPI_CS: U1.A18, U22.5
/Principal/BANK_501/SPI_MISO: U1.B19, U22.3
/Principal/BANK_501/SPI_MOSI: U1.E17, U22.2
/Principal/BANK_501/USB_B_N: J16.2, TR2.4, U44.3
/Principal/BANK_501/USB_B_P: J16.3, TR2.1, U44.2
/Principal/BANK_501/USB_CLK: U1.K16, U41.1
/Principal/BANK_501/USB_D0: U1.K17, U41.3
/Principal/BANK_501/USB_D1: U1.E22, U41.4
/Principal/BANK_501/USB_D2: U1.J16, U41.5
/Principal/BANK_501/USB_D3: U1.D19, U41.6
/Principal/BANK_501/USB_D4: U1.J18, U41.7
/Principal/BANK_501/USB_D5: U1.D20, U41.9
/Principal/BANK_501/USB_D6: U1.D21, U41.10
/Principal/BANK_501/USB_D7: U1.C21, U41.13
/Principal/BANK_501/USB_DIR: U1.E20, U41.31
/Principal/BANK_501/USB_ID: D8.2, J16.4, U41.23
/Principal/BANK_501/USB_N: TR2.3, U41.19
/Principal/BANK_501/USB_NXT: U1.E21, U41.2
/Principal/BANK_501/USB_P: TR2.2, U41.18
/Principal/BANK_501/USB_STP: U1.K19, U41.29
/Principal/BANK_502/DDR_A0: R3.2, U1.K22, U2.N3, U3.N3
/Principal/BANK_502/DDR_A1: R4.2, U1.K20, U2.P7, U3.P7
/Principal/BANK_502/DDR_A2: R5.2, U1.N21, U2.P3, U3.P3
/Principal/BANK_502/DDR_A3: R6.2, U1.L22, U2.N2, U3.N2
/Principal/BANK_502/DDR_A4: R7.2, U1.M20, U2.P8, U3.P8
/Principal/BANK_502/DDR_A5: R8.2, U1.N22, U2.P2, U3.P2
/Principal/BANK_502/DDR_A6: R9.2, U1.L20, U2.R8, U3.R8
/Principal/BANK_502/DDR_A7: R10.2, U1.J21, U2.R2, U3.R2
/Principal/BANK_502/DDR_A8: R11.2, U1.T20, U2.T8, U3.T8
/Principal/BANK_502/DDR_A9: R12.2, U1.U20, U2.R3, U3.R3
/Principal/BANK_502/DDR_A10: R13.2, U1.M22, U2.L7, U3.L7
/Principal/BANK_502/DDR_A11: R14.2, U1.H21, U2.R7, U3.R7
/Principal/BANK_502/DDR_A12: R15.2, U1.P20, U2.N7, U3.N7
/Principal/BANK_502/DDR_A13: R16.2, U1.J20, U2.T3, U3.T3
/Principal/BANK_502/DDR_A14: R17.2, U1.R20, U2.T7, U3.T7
/Principal/BANK_502/DDR_BA0: R18.2, U1.U22, U2.M2, U3.M2
/Principal/BANK_502/DDR_BA1: R19.2, U1.T22, U2.N8, U3.N8
/Principal/BANK_502/DDR_BA2: R20.2, U1.R22, U2.M3, U3.M3
/Principal/BANK_502/DDR_CAS: R21.2, U1.Y23, U2.K3, U3.K3
/Principal/BANK_502/DDR_CKE: R22.2, U1.U21, U2.K9, U3.K9
/Principal/BANK_502/DDR_CLK_N: R27.1, U1.P21, U2.K7, U3.K7
/Principal/BANK_502/DDR_CLK_P: R27.2, U1.R21, U2.J7, U3.J7
/Principal/BANK_502/DDR_CS: R23.2, U1.Y21, U2.L2, U3.L2
/Principal/BANK_502/DDR_DM0: U1.G24, U2.E7
/Principal/BANK_502/DDR_DM1: U1.K25, U2.D3
/Principal/BANK_502/DDR_DM2: U1.P26, U3.E7
/Principal/BANK_502/DDR_DM3: U1.V26, U3.D3
/Principal/BANK_502/DDR_DQ0: U1.J26, U2.E3
/Principal/BANK_502/DDR_DQ1: U1.F25, U2.F7
/Principal/BANK_502/DDR_DQ2: U1.J25, U2.F2
/Principal/BANK_502/DDR_DQ3: U1.G26, U2.F8
/Principal/BANK_502/DDR_DQ4: U1.H26, U2.H3
/Principal/BANK_502/DDR_DQ5: U1.H23, U2.H8
/Principal/BANK_502/DDR_DQ6: U1.J24, U2.G2
/Principal/BANK_502/DDR_DQ7: U1.J23, U2.H7
/Principal/BANK_502/DDR_DQ8: U1.K26, U2.D7
/Principal/BANK_502/DDR_DQ9: U1.L23, U2.C3
/Principal/BANK_502/DDR_DQ10: U1.M26, U2.C8
/Principal/BANK_502/DDR_DQ11: U1.K23, U2.C2
/Principal/BANK_502/DDR_DQ12: U1.M25, U2.A7
/Principal/BANK_502/DDR_DQ13: U1.N24, U2.A2
/Principal/BANK_502/DDR_DQ14: U1.M24, U2.B8
/Principal/BANK_502/DDR_DQ15: U1.N23, U2.A3
/Principal/BANK_502/DDR_DQ16: U1.R26, U3.E3
/Principal/BANK_502/DDR_DQ17: U1.P24, U3.F7
/Principal/BANK_502/DDR_DQ18: U1.N26, U3.F2
/Principal/BANK_502/DDR_DQ19: U1.P23, U3.F8
/Principal/BANK_502/DDR_DQ20: U1.T24, U3.H3
/Principal/BANK_502/DDR_DQ21: U1.T25, U3.H8
/Principal/BANK_502/DDR_DQ22: U1.T23, U3.G2
/Principal/BANK_502/DDR_DQ23: U1.R23, U3.H7
/Principal/BANK_502/DDR_DQ24: U1.V24, U3.D7
/Principal/BANK_502/DDR_DQ25: U1.U26, U3.C3
/Principal/BANK_502/DDR_DQ26: U1.U24, U3.C8
/Principal/BANK_502/DDR_DQ27: U1.U25, U3.C2
/Principal/BANK_502/DDR_DQ28: U1.W26, U3.A7
/Principal/BANK_502/DDR_DQ29: U1.Y25, U3.A2
/Principal/BANK_502/DDR_DQ30: U1.Y26, U3.B8
/Principal/BANK_502/DDR_DQ31: U1.W23, U3.A3
/Principal/BANK_502/DDR_DQS0_N: U1.G25, U2.G3
/Principal/BANK_502/DDR_DQS0_P: U1.H24, U2.F3
/Principal/BANK_502/DDR_DQS1_N: U1.L25, U2.B7
/Principal/BANK_502/DDR_DQS1_P: U1.L24, U2.C7
/Principal/BANK_502/DDR_DQS2_N: U1.R25, U3.G3
/Principal/BANK_502/DDR_DQS2_P: U1.P25, U3.F3
/Principal/BANK_502/DDR_DQS3_N: U1.W25, U3.B7
/Principal/BANK_502/DDR_DQS3_P: U1.W24, U3.C7
/Principal/BANK_502/DDR_ODT: R24.2, U1.Y22, U2.K1, U3.K1
/Principal/BANK_502/DDR_RAS: R25.2, U1.V23, U2.J3, U3.J3
/Principal/BANK_502/DDR_RESET: R28.1, U1.H22, U2.T2, U3.T2
/Principal/BANK_502/DDR_WE: R26.2, U1.V22, U2.L3, U3.L3
/Principal/Expansion/GPIO0_B: J10.5, U20.13
/Principal/Expansion/GPIO1_B: J10.6, U20.12
/Principal/Expansion/GPIO2_B: J10.7, U20.11
/Principal/Expansion/GPIO3_B: J10.8, U20.10
/Principal/Expansion/GPIO4_B: J10.9, U21.13
/Principal/Expansion/GPIO5_B: J10.10, U21.12
/Principal/Expansion/GPIO6_B: J10.11, U21.11
/Principal/Expansion/GPIO7_B: J10.12, U21.10
/Principal/Expansion/SPI_CLK_B: J10.14, U22.11
/Principal/Expansion/SPI_CS_B: J10.16, U22.10
/Principal/Expansion/SPI_MISO_B: J10.15, U22.12
/Principal/Expansion/SPI_MOSI_B: J10.13, U22.13
/Principal/OneBank/BTM_0CK_N: J3.38, U11.28
/Principal/OneBank/BTM_0CK_P: J3.36, U11.29
/Principal/OneBank/BTM_0RX_N: J3.26, U11.35
/Principal/OneBank/BTM_0RX_P: J3.24, U11.36
/Principal/OneBank/BTM_0TX_N: J3.14, U11.37
/Principal/OneBank/BTM_0TX_P: J3.12, U11.38
/Principal/OneBank/BTM_1CK_N: J2.38, J3.37
/Principal/OneBank/BTM_1CK_P: J2.36, J3.35
/Principal/OneBank/BTM_1RX_N: J2.26, J3.25
/Principal/OneBank/BTM_1RX_P: J2.24, J3.23
/Principal/OneBank/BTM_1TX_N: J2.14, J3.13
/Principal/OneBank/BTM_1TX_P: J2.12, J3.11
/Principal/OneBank/BTM_2CK_N: J2.37, J3.43
/Principal/OneBank/BTM_2CK_P: J2.35, J3.41
/Principal/OneBank/BTM_2RX_N: J2.25, J3.31
/Principal/OneBank/BTM_2RX_P: J2.23, J3.29
/Principal/OneBank/BTM_2TX_N: J2.13, J3.19
/Principal/OneBank/BTM_2TX_P: J2.11, J3.17
/Principal/OneBank/BTM_3CK_N: J2.43, J3.44
/Principal/OneBank/BTM_3CK_P: J2.41, J3.42
/Principal/OneBank/BTM_3RX_N: J2.31, J3.32
/Principal/OneBank/BTM_3RX_P: J2.29, J3.30
/Principal/OneBank/BTM_3TX_N: J2.19, J3.20
/Principal/OneBank/BTM_3TX_P: J2.17, J3.18
/Principal/OneBank/MGTXTX0_B_N: C108.2, U11.7
/Principal/OneBank/MGTXTX0_B_P: C107.2, U11.6
/Principal/OneBank/OB_3V3: J2.3, J2.4, J3.3, J3.4
/Principal/OneBank/OB_ALERT: J2.51, J3.51
/Principal/OneBank/OB_DIR: C273.1, J2.45, J3.45, R64.2
/Principal/OneBank/OB_PE_RST: J2.2, J3.2
/Principal/OneBank/OB_PG: C274.1, J2.46, J3.46
/Principal/OneBank/OB_PSON: C275.1, J2.52, J3.52
/Principal/OneBank/OB_USB0_N: J2.8, J3.8
/Principal/OneBank/OB_USB0_P: J2.6, J3.6
/Principal/OneBank/OB_USB1_N: J2.7, J3.7
/Principal/OneBank/OB_USB1_P: J2.5, J3.5
/Principal/OneBank/OB_USB_OC: J2.1, J3.1
/Principal/OneBank/TOP_3CK_N: J2.44, U11.24
/Principal/OneBank/TOP_3CK_P: J2.42, U11.25
/Principal/OneBank/TOP_3RX_N: J2.32, U11.31
/Principal/OneBank/TOP_3RX_P: J2.30, U11.32
/Principal/OneBank/TOP_3TX_N: J2.20, U11.33
/Principal/OneBank/TOP_3TX_P: J2.18, U11.34
/Principal/PMIC/VDDD: C102.2, R57.2, U9.20, U9.39
/Principal/RTC-HDMI/VOUT_HDMI: C118.2, J4.18, U14.5
DDR_VTT: C55.2, C56.2, C57.2, C58.2, C59.2, C60.2, C61.1, C62.1, C70.2, R3.1, R4.1, R5.1, R6.1, R7.1, R8.1, R9.1, R10.1, R11.1, R12.1, R13.1, R14.1, R15.1, R16.1, R17.1, R18.1, R19.1, R20.1, R21.1, R22.1, R23.1, R24.1, R25.1, R26.1, U4.3, U4.5
GND: BT1.2, C1.1, C2.1, C3.2, C4.1, C5.1, C6.2, C7.1, C8.2, C9.2, C10.1, C11.2, C12.2, C13.1, C14.2, C15.2, C16.1, C17.2, C18.2, C19.1, C20.2, C21.2, C22.1, C23.2, C24.2, C25.1, C26.2, C27.2, C28.1, C29.1, C30.2, C31.1, C32.1, C33.2, C34.1, C35.2, C36.2, C37.1, C38.2, C39.2, C40.1, C41.2, C42.2, C43.1, C44.2, C45.2, C46.1, C47.2, C48.2, C49.1, C50.2, C51.2, C52.1, C53.2, C54.2, C55.1, C56.1, C57.1, C58.1, C59.1, C60.1, C61.2, C62.2, C63.1, C64.1, C65.1, C66.1, C67.1, C68.2, C69.2, C70.1, C71.1, C76.2, C77.2, C78.2, C79.2, C80.1, C81.1, C82.1, C83.1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
unnamed: BT1.1, U12.3
unnamed: C67.2, R36.2, R37.2, U5.18
unnamed: C72.1, C73.1, L1.1, R39.1, U5.6, U5.7, U5.8, U5.9, U5.10, U5.11
unnamed: C72.2, R42.1
unnamed: C73.2, R38.2
unnamed: C74.1, C75.1, R39.2
unnamed: C75.2, R44.1, R45.2, U5.1
unnamed: C84.1, U9.45
unnamed: C85.2, U9.24
unnamed: C87.2, R47.1
unnamed: C88.2, R48.1
unnamed: C89.1, U8.6
unnamed: C89.2, L2.1, U8.2
unnamed: C91.2, R47.2, U9.46
unnamed: C92.2, R48.2, U9.25
unnamed: C94.1, U9.1
unnamed: C94.2, L3.1, U9.2, U9.3, U9.4
unnamed: C95.1, U9.28
unnamed: C95.2, L4.1, U9.29
unnamed: C96.2, U9.18
unnamed: C97.2, U9.16
unnamed: C98.2, U9.37
unnamed: C99.2, U9.19
unnamed: C100.2, R55.1
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
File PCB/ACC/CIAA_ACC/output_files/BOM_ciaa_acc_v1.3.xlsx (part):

Source: | /home/noelia/git/CIAA_gitlab/CIAA-ACC/pcb/ciaa_acc.sch
Date: | Fri 29 Mar 2019 08:47:07 AM -03
Tool: | Eeschema 5.0.2+dfsg1-1~bpo9+1
Generator: | bom_csv_grouped_by_value.py
Component Count: | 561
Item | Qty | Reference(s) | Value | Footprint | Desc | Digikey# | Manf | Manf# | Mouser# | Reemplazo
1 | 1 | BT1 | CR1220 | conn:BC501SM | HOLDER COIN CELL FOR CR1220 SMD | BC501SM-ND | MPD | BC501SM
2 | 23 | C1, C28, C55, C56, C65, C66, C80, C81, C82, C83, C86, C161, C163, C167, C180, C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 | 100uF | chip_rlc:c_1206 | 100µF ±20% 6.3V X6T Ceramic Capacitor -55°C ~ 105°C Surface Mount, MLCC 1206 (3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 | 490-10525-1-ND | Murata | GRM31CD80J107ME39L
3 | 97 | C2, C5, C10, C13, C16, C19, C22, C25, C29, C32, C37, C40, C43, C46, C49, C52, C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 | 100nF | chip_rlc:c_0201 | CAP CER 0.1UF 10V X5R 0201 | 490-5405-1-ND | Murata | GRM033R61A104ME15D
4 | 47 | C3, C6, C8, C9, C11, C12, C14, C15, C17, C18, C20, C21, C23, C24, C26, C27, C30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 | 10nF | chip_rlc:c_0201 | 10000pF ±10% 16V X5R Ceramic Capacitor -55°C ~ 85°C Surface Mount, MLCC 0201 (0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 | 490-7223-1-ND | Murata | GRM033R61C103KA12D
5 | 45 | C4, C7, C31, C34, C57, C58, C68, C70, C77, C90, C96, C119, C120, C121, C122, C1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 | 10uF | chip_rlc:c_0402 | 10µF 6.3V Ceramic Capacitor X6S 0402 (1005 Metric) 0.039" L x 0.020" W (1.00mm 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 | 490-13233-1-ND | Murata | GRM155C80J106ME11D
6 | 1 | C67 | 470nF | chip_rlc:c_0402 | 0.47µF ±10% 35V X5R Ceramic Capacitor -55°C ~ 85°C Surface Mount, MLCC 0402 (10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 | 490-10462-1-ND | Murata | GRM155R6YA474KE01D
7 | 1 | C71 | 220nF | chip_rlc:c_0402 | 0.22µF ±10% 35V X6S Ceramic Capacitor -55°C ~ 105°C Surface Mount, MLCC 0402 (1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 | 490-10445-1-ND | Murata | GRM155C8YA224KE01D
8 | 2 | C72, C87 | 2.2nF | chip_rlc:c_0402 | 2200pF ±10% 16V X7R Ceramic Capacitor -55°C ~ 125°C Surface Mount, MLCC 0402 (1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 | 490-6330-1-ND | Murata | GRM155R71C222KA01D
9 | 1 | C73 | 47nF | chip_rlc:c_0402 | 0.047µF ±10% 25V X7R Ceramic Capacitor -55°C ~ 125°C Surface Mount, MLCC 0402 (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 | 490-6347-1-ND | Murata | GRM155R71E473KA88J
10 | 1 | C74 | 22nF | chip_rlc:c_0402 | 0.022µF ±10% 50V X7R Ceramic Capacitor -55°C ~ 125°C Surface Mount, MLCC 0402 (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 | 490-3884-1-ND | Murata | GRM155R71H223KA12D
11 | 1 | C75 | 1nF | chip_rlc:c_0402 | CAP CER 1000PF 50V NP0 0402 | 399-10034-1-ND | Murata | C0402C102J5GACTU
12 | 7 | C76, C78, C79, C162, C166, C170, C174 | 330uF | tantalum:tant_B_3528 | CAP TANT 330UF 2.5V 20% SMD | 399-11709-1-ND | Kemet | T520B337M2R5ATE009
13 | 4 | C84, C85, C97, C98 | 68nF | chip_rlc:c_0402 | 0.068µF ±10% 50V X7R Ceramic Capacitor -55°C ~ 125°C Surface Mount, MLCC 0402 (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 | 490-12709-1-ND | Murata | GRM155R71H683KE14D
14 | 2 | C88, C101 | 1.2nF | chip_rlc:c_0402 | 1200pF ±10% 50V X7R Ceramic Capacitor -55°C ~ 125°C Surface Mount, MLCC 0402 (1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 | 490-1304-1-ND | Murata | GRM155R71H122KA01D
15 | 1 | C91 | 24pF | chip_rlc:c_0402 | 24pF ±5% 50V C0G, NP0 Ceramic Capacitor -55°C ~ 125°C Surface Mount, MLCC 0402 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 | 490-5931-1-ND | Murata | GRM1555C1H240JA01D
16 | 1 | C92 | 11pF | chip_rlc:c_0402 | 11pF ±5% 50V C0G, NP0 Ceramic Capacitor -55°C ~ 125°C Surface Mount, MLCC 0402 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 | 490-5923-1-ND | Murata | GRM1555C1H110JA01D
17 | 2 | C99, C244 | 4.7uF | chip_rlc:c_0603 | CAP CER 4.7UF 10V X5R 0603 | 490-10477-1-ND | Murata | GRM188R61A475KE15D
18 | 5 | C100, C138, C139, C140, C141 | 1.5nF | chip_rlc:c_0402 | 1500pF ±10% 50V X7R Ceramic Capacitor -55°C ~ 125°C Surface Mount, MLCC 0402 (1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 | 490-3245-1-ND | Murata | GRM155R71H152KA01D
19 | 1 | C102 | 3.3uF | chip_rlc:c_0603 | 3.3µF ±10% 10V X5R Ceramic Capacitor -55°C ~ 85°C Surface Mount, MLCC 0603 (160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 | 490-6411-1-ND | Murata | GRM188R61A335KE15D
20 | 1 | C103 | 16pF | chip_rlc:c_0402 | 16pF ±5% 50V C0G, NP0 Ceramic Capacitor -55°C ~ 125°C Surface Mount, MLCC 0402 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 | 490-5926-1-ND | Murata | GRM1555C1H160JA01D
21 | 1 | C104 | 13pF | chip_rlc:c_0402 | 13pF ±5% 50V C0G, NP0 Ceramic Capacitor -55°C ~ 125°C Surface Mount, MLCC 0402 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 | 490-5925-1-ND | Murata | GRM1555C1H130JA01D
22 | 2 | C112, C113 | 18pF | chip_rlc:c_0201 | CAP CER 18PF 50V NP0 0201 | 490-6117-2-ND | Murata | GRM0335C1H180JA01D
23 | 8 | C129, C131, C159, C238, C239, C240, C256, C261 | 100nF | chip_rlc:c_0402 | CAP CER 0.1UF 10V X5R 0402 | 311-1336-1-ND | Yageo | CC0402KRX5R6BB104
24 | 27 | C164, C168, C172, C176, C177, C179, C181, C183, C185, C187, C189, C191, C192, C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 | 1uF | chip_rlc:c_0201 | 1µF 10V Ceramic Capacitor X5R 0201 (0603 Metric) 0.024" L x 0.012" W (0.60mm x 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 | 1276-6816-1-ND | Samsung | CL03A105MP3ZSNH
25 | 1 | C237 | 2.2uF | chip_rlc:c_0402 | CAP CER 2.2UF 6.3V X5R 0402 | 490-12532-2-ND | Murata | GRM155R60J225KE95D
26 | 3 | D1, D4, D5 | PESD3V3U1UA | to-sod-sot:SOD-323 | TVS DIODE 3.3VWM SOD323 | 568-4667-1-ND | NXP | PESD3V3U1UA,115
27 | 5 | D2, D3, D6, D7, D9 | 1N4148 | to-sod-sot:SOD-323 | DIODE GEN PURP 75V 150MA SOD323 | 1N4148WXTPMSCT-ND | Micro Commercial | 1N4148WX-TP
28 | 1 | D8 | SD05T1G | to-sod-sot:SOD-323 | TVS DIODE 5VWM 9.8VC SOD323 | SD05T1GOSCT-ND | ON Semiconductor | SD05T1G
29 | 2 | DS2, DS13 | ERR | misc:LED-0603 | LED RED CLEAR 0603 SMD | 1080-1400-1-ND | Everlight | QTLP600C7TR
30 | 2 | DS3, DS12 | OK | misc:LED-0603 | LED GREEN CLEAR 0603 SMD | 1080-1399-1-ND | Everlight | QTLP600C4TR
31 | 1 | DS4 | DONE | misc:LED-0603 | LED BLUE CLEAR 0603 SMD | 1080-1401-1-ND | Everlight | QTLP600CBTR
32 | 1 | DS5 | CONNECTED | misc:LED-0603 | LED GREEN CLEAR 0603 SMD | 1080-1399-1-ND | Everlight | QTLP600C4TR
33 | 1 | DS6 | RUNNING | misc:LED-0603 | LED BLUE CLEAR 0603 SMD | 1080-1401-1-ND | Everlight | QTLP600CBTR
34 | 8 | DS7, DS8, DS9, DS10, DS14, DS15, DS16, DS17 | LED | misc:LED-0603 | LED RED CLEAR 0603 SMD | 1080-1400-1-ND | Everlight | QTLP600C7TR
35 | 1 | DS11 | OVERCURRENT | misc:LED-0603 | LED RED CLEAR 0603 SMD | 1080-1400-1-ND | Everlight | QTLP600C7TR
36 | 4 | F1, F2, F3, F4 | FIDUCIAL | misc:Fiducial_1mm | FIDUCIAL
37 | 3 | FB3, FB7, FB8 | BLM15PX221SN1D | chip_rlc:l_0402 | 220 Ohm Impedance Ferrite Bead 0402 (1005 Metric) Surface Mount Power Line 1.4A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 | 490-11021-1-ND | Murata | BLM15PX221SN1D
38 | 4 | FB4, FB5, FB6, FB9 | MMZ1608B601CTAH0 | chip_rlc:l_0603 | FERRITE BEAD 600 OHM 0603 1LN | 445-2166-1-ND | TDK | MMZ1608B601CTAH0
39 | 3 | FB10, FB11, FB12 | MPZ1608S601ATA00 | chip_rlc:l_0603 | FERRITE BEAD 600 OHM 0603 1LN | 445-2205-1-ND | TDK | MPZ1608S601ATA00
44 | 1 | J1 | 5V 10A | conn:PJ-082BH | Power Barrel Connector Jack 2.50mm ID (0.098"), 5.50mm OD (0.217") Through Hole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 | CP-082BHCT-ND | CUI | PJ-082BH
45 | 1 | J2 | OneBank Top | samtec:ASP-129637-13 | PCIe104 OneBank Top |  | Samtec | ASP-129637-13
46 | 1 | J3 | OneBank Bottom | samtec:ASP-129646-22 | PCIe104 OneBank Bottom |  | Samtec | ASP-129646-22
47 | 1 | J4 | HDMI | conn:10029449-111RLF | HDMI Receptacle Connector 19 Position Surface Mount, Right Angle, Horizontal | 609-4614-1-ND | Amphenol FCI | 10029449-111RLF
48 | 1 | J5 | FMC_HPC | samtec:ASP-134486-01 | FMC HPC |  | Samtec | ASP-134486-01 |  | ASP-134485-01
49 | 1 | J6 | JTAG DIRECT | conn:PIN_ARRAY_5x2_1.27_SMD | CONN HDR 1.27MM SMD AU 10POS | 952-1389-ND | Harwin | M50-3600542
50 | 1 | J7 | CAS-D20TA | misc:CAS-D20TA | SLIDE SWITCH SPDT 2POS J HOOK 6V | CASD20JCT-ND | Copal Electronics | CAS-D20TA
51 | 1 | J8 | USB Micro B | conn:ZX62-AB-5PA | USB - micro B USB 2.0 Receptacle Connector 5 Position Surface Mount, Right Angl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 | H125270CT-ND | Hirose | ZX62-B-5PA(33)
52 | 1 | J9 | FAN | conn:B2B-PH-SM4-TB | 2 Positions Header, Shrouded Connector 0.079" (2.00mm) Surface Mount Tin | 455-1734-1-ND | JST | B2B-PH-SM4-TB(LF)(SN)
53 | 1 | J10 | DNP | conn:Pin_Header_Straight_2x10_SMD | 20 Positions Header, Unshrouded, Breakaway Connector 0.100" (2.54mm) Surface Mo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 | 952-2550-ND | Harwin | M20-8761042
54 | 1 | J11 | DIGITAL IN | conn:1770940 | CONN TERM BLK 8POS 2.5MM | 277-2085-1-ND | Phoenix Contact | 1770940
55 | 1 | J12 | DIGITAL OUT | conn:1770940 | CONN TERM BLK 8POS 2.5MM | 277-2085-1-ND | Phoenix Contact | 1770940
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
